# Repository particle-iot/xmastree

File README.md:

# PARTICLE CHRISTMAS TREE

It's a Happy Hardware Holiday for all! Meet the Particle Christmas Tree, a limited edition PCB packed full of cheer with customizable light patterns and holiday tunes. Use your tree with a Particle Photon or Electron to light up the LEDs and play music. Control your tree from the onboard joystick or from the Christmas Tree Web App.

Learn how to get started below. Happy Holidays from Team Particle!

## THINGS YOU'LL NEED
 - Christmas Tree
 - Micro USB cable
 - USB power supply (2A minimum rating)
 - Your Photon or Electron (new to Particle? Get started [here](https://docs.particle.io/guide/getting-started).)
 - Eggnog (optional)

## STEPS 

You can setup the tree in a matter of minutes.

1. Insert the Photon into the socket
1. Plug in the USB power supply
1. Flash [the Christmas tree firmware from the Web IDE][Firmware shared app] - no downloads required.
1. [Open the web interface][Web interface] and spread the cheer!

[Firmware shared app]: https://go.particle.io/shared_apps/5fc8c888e6f0b000092cf113
[Web interface]: https://particle-iot.github.io/xmastree

## GET TO KNOW YOUR TREE

### Joystick

The joystick is a 5 way button: up, down, left, right, and center (push in) then you can reprogram the usage any way you'd like. We have setup the button for you in the Christmas tree firmware to toggle light patterns and music.

|DIR   | PIN |
|:---  |:--- |
|UP    |D4| 
|DOWN  |A0|
|LEFT  |D5|
|RIGHT |D3|
|CENTER|D6|

### Dotstar RGB LEDs

The tree has 25 of the [APA102](http://www.led-color.com/upload/201604/APA102-2020%20SMD%20LED.pdf) 2020 RGB LEDs (also commonly known as dotstars) connected in a daisy chain. These LEDs are individually addressable using two pins, data and clock. These tiny stars are incredibly bright and fast. At full brightness, with all colors turned ON, each LED will consume about 60mA of current. So 25 of them will consume a max of 1.5Amp. This is why we recommend powering the tree with a **5VDC power supply that can source at least 2Amp.** Most modern USB phone chargers should be able to meet this demand.

### Photon/Electron Socket

The two dual-row headers allow you to use either the Particle Photon or the Electron. Please take care of the orientation and position of the device while plugging in.

### Piezo speaker

At the back of the tree you'll find a piezo speaker connected to pin D0. The firmware includes several 8-bit holiday tunes but you can also compose your own. This speaker can be a bit loud. If you'd like to reduce the volume, you can put a piece of tape on its opening.

### Headers for breadboarding

These pins breakout the power and control signal of the tree. You can mount the tree on a breadboard with the help of these pins. This will allow you to connect different hardware to your tree, daisy chain multiple trees, add more LEDs or even control it with other microcontrollers.

|PIN     |DESCRIPTION|
|:-------|:----------|
|D1      | Connected to the D1 pin of the Particle device and acts as CLOCK IN to the LEDs.|
|D2      | Connected to the D2 pin of the Particle device and acts as DATA IN to the LEDs.|
|DATA OUT| DATA OUT pin of the LEDs.|
|CLK OUT | CLOCK OUT pin of the LEDs.|
|VIN     | Input power to the tree and Particle device. This pin is connected to the VIN pin of the Particle device. 5VDC max .|
|GND     | Connected to the ground.|

## SETTING UP THE TREE 

You can either use a Particle Photon or an Electron to control the tree. Since the dotstar RGB LEDs work at 5VDC, you'll need to make sure that the USB cable is plugged in at all times to power the tree, unless you have powered the tree via a separate power source via the VIN pin.

> **NOTE:** When controlled by an Electron, the tree will not work with just the LiPo battery plugged in. You'll need to connect the USB cable as well or other external 5V DC power source.

## WAYS TO SET UP THE TREE

### As an ornament

The easiest way to setup the tree is to hang it as an ornament while powering over USB. You can also rig up your own 5V power supply cable and plug it into the header.

### On a breadboard

You can use the bottom header to mount the tree on a breadboard and power/control it via your own choice of hardware or to daisy chain the tree to other trees or dotstar projects.

## USING THE WEB INTERFACE

<p align="center">
</p>

There is [a hosted version of the web interface you can use to control your tree][Web interface]. Simply login with your Particle account, select your device and you'll be able to control the LEDs and music from a desktop or mobile browser.

## MODIFYING THE FIRMWARE

[][Firmware shared app]

Import the firmware to your Particle account in the Web IDE with the button above. You'll be
able to add new songs or tweak the functionality to your heart's
content.

Click [here](FIRMWARE.md) for more information about the Xmas Tree firmware.

## CONNECT

Having problems or have awesome suggestions? Connect with us on our [forum](https://community.particle.io/).

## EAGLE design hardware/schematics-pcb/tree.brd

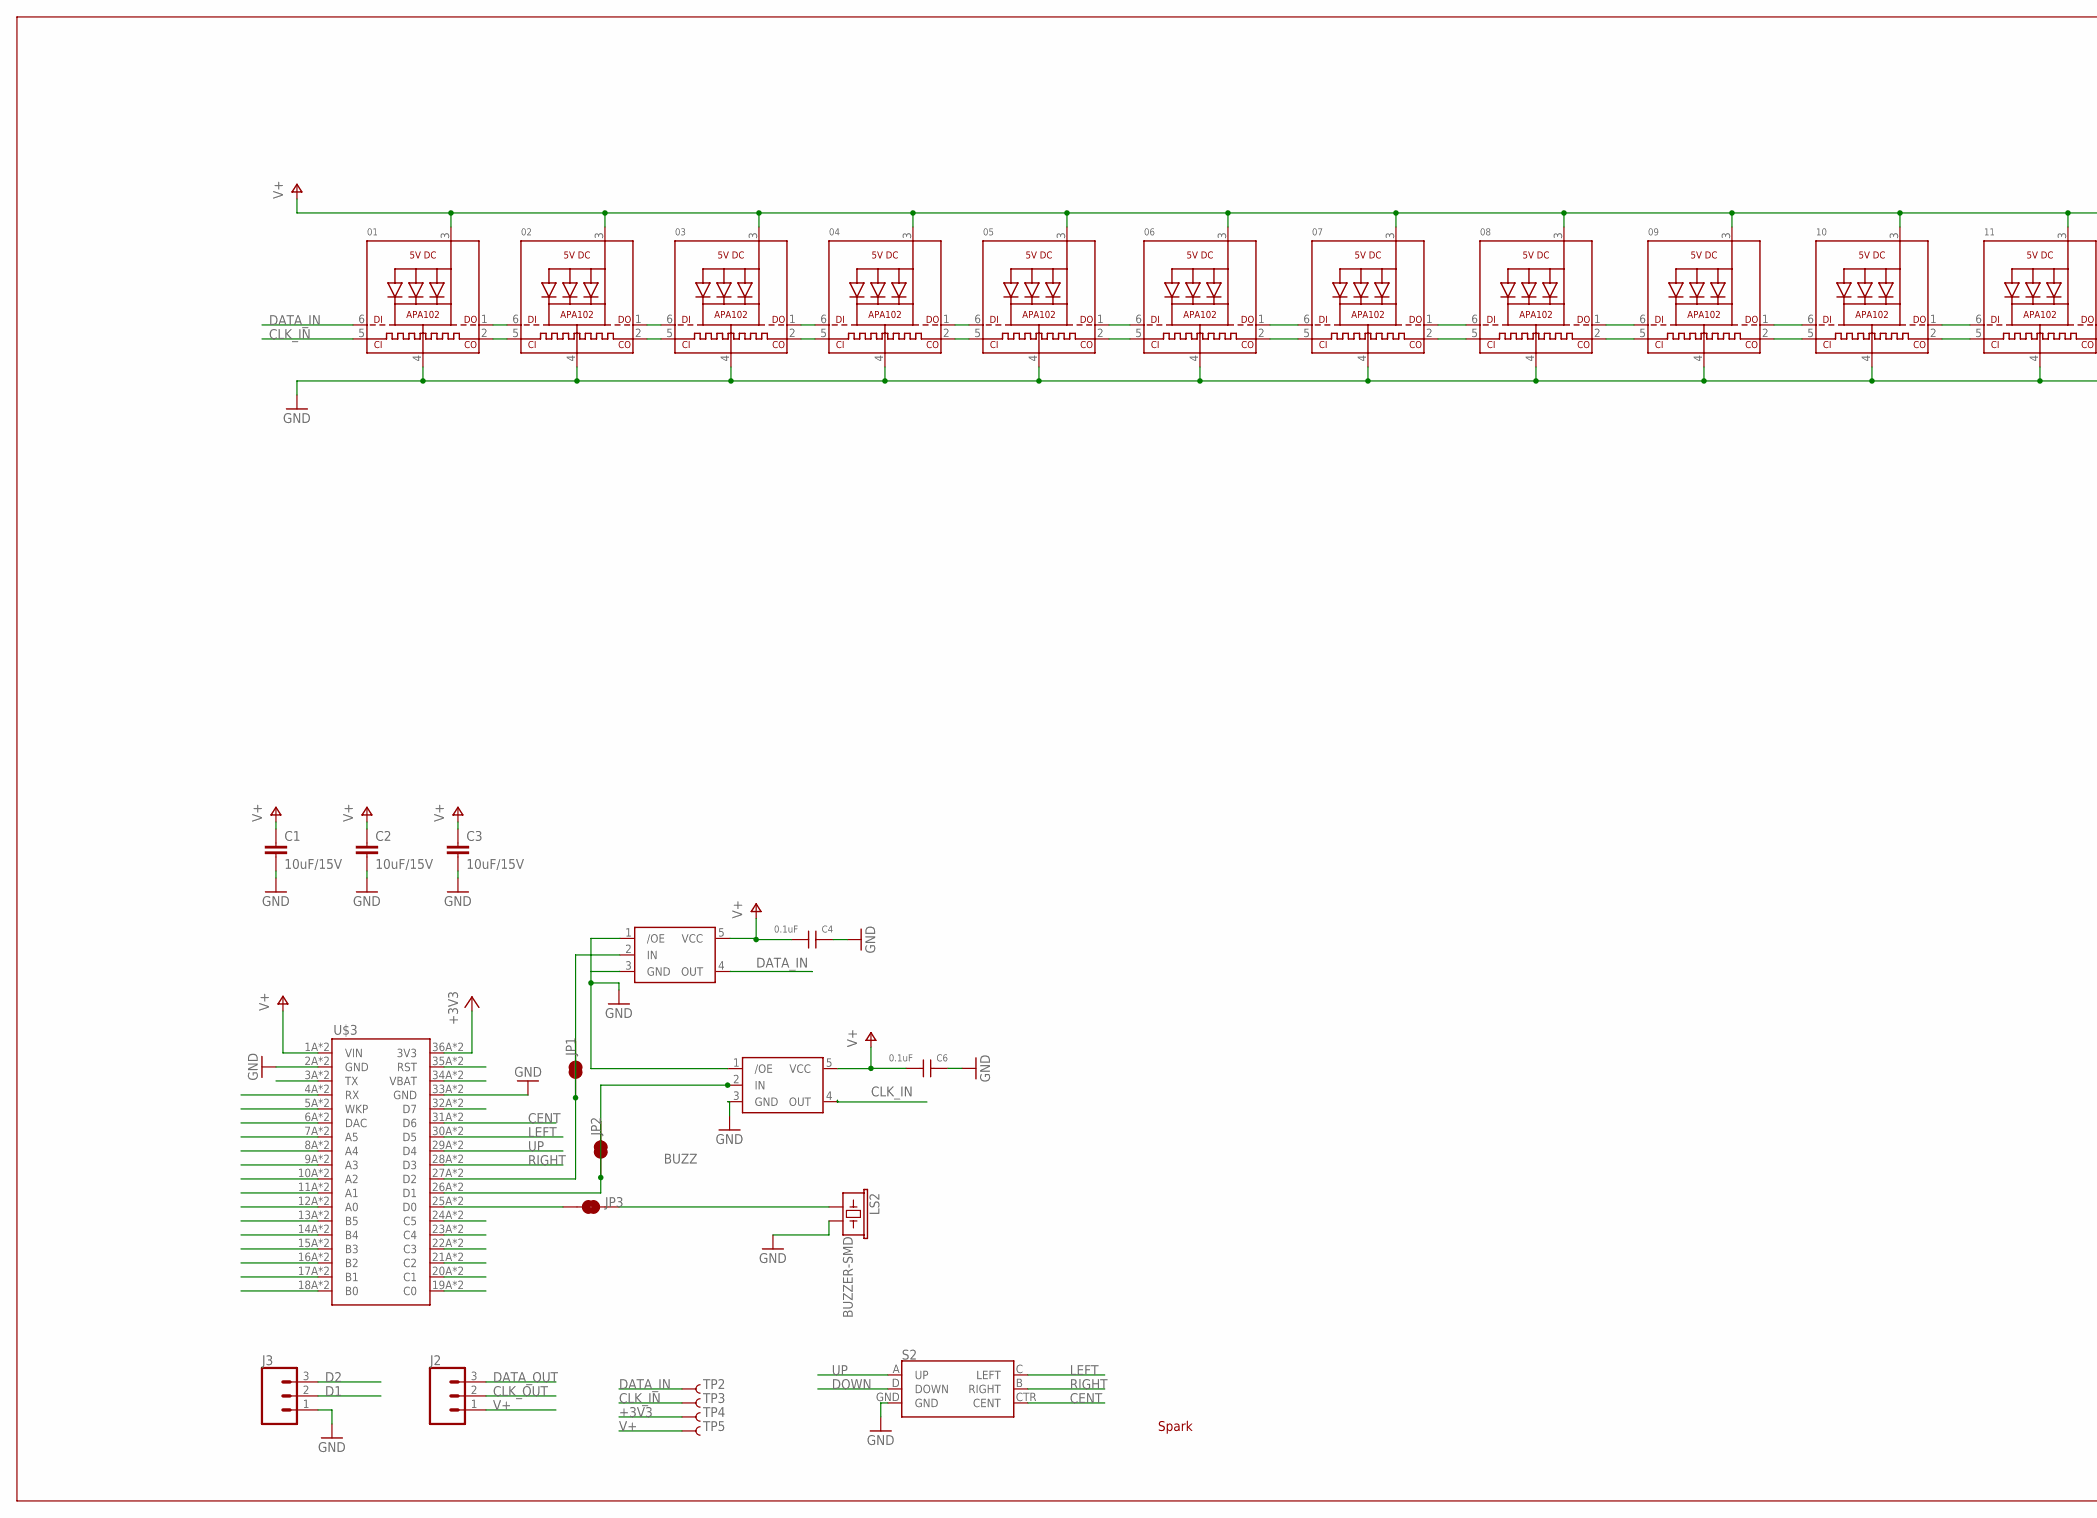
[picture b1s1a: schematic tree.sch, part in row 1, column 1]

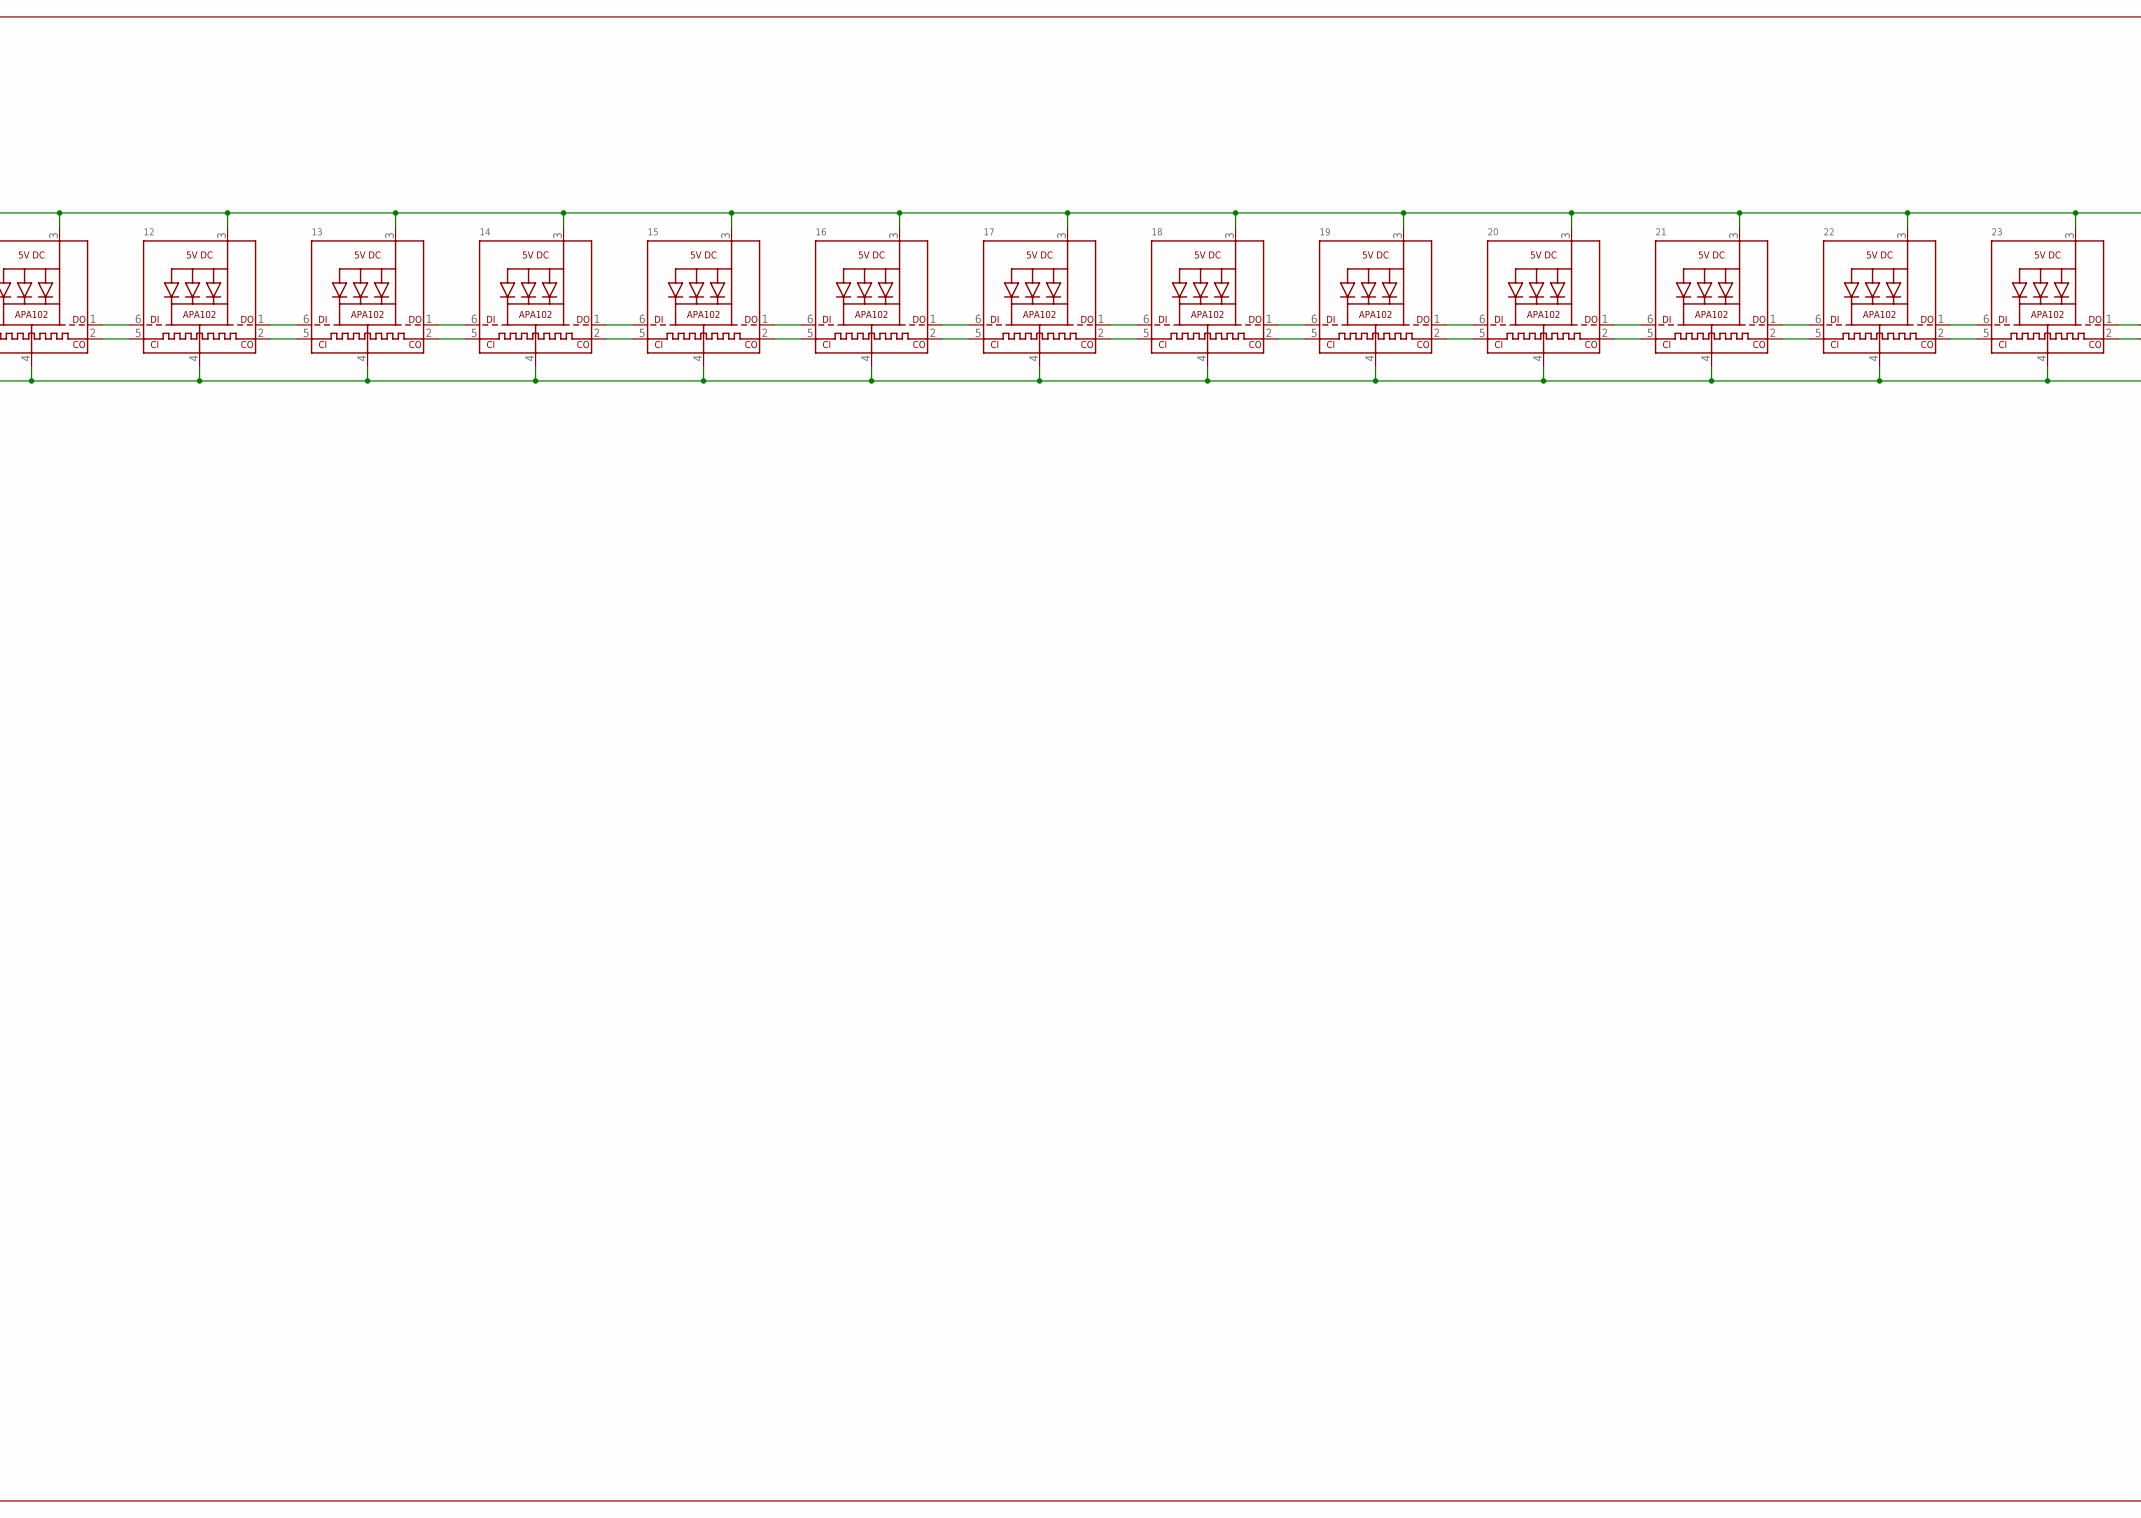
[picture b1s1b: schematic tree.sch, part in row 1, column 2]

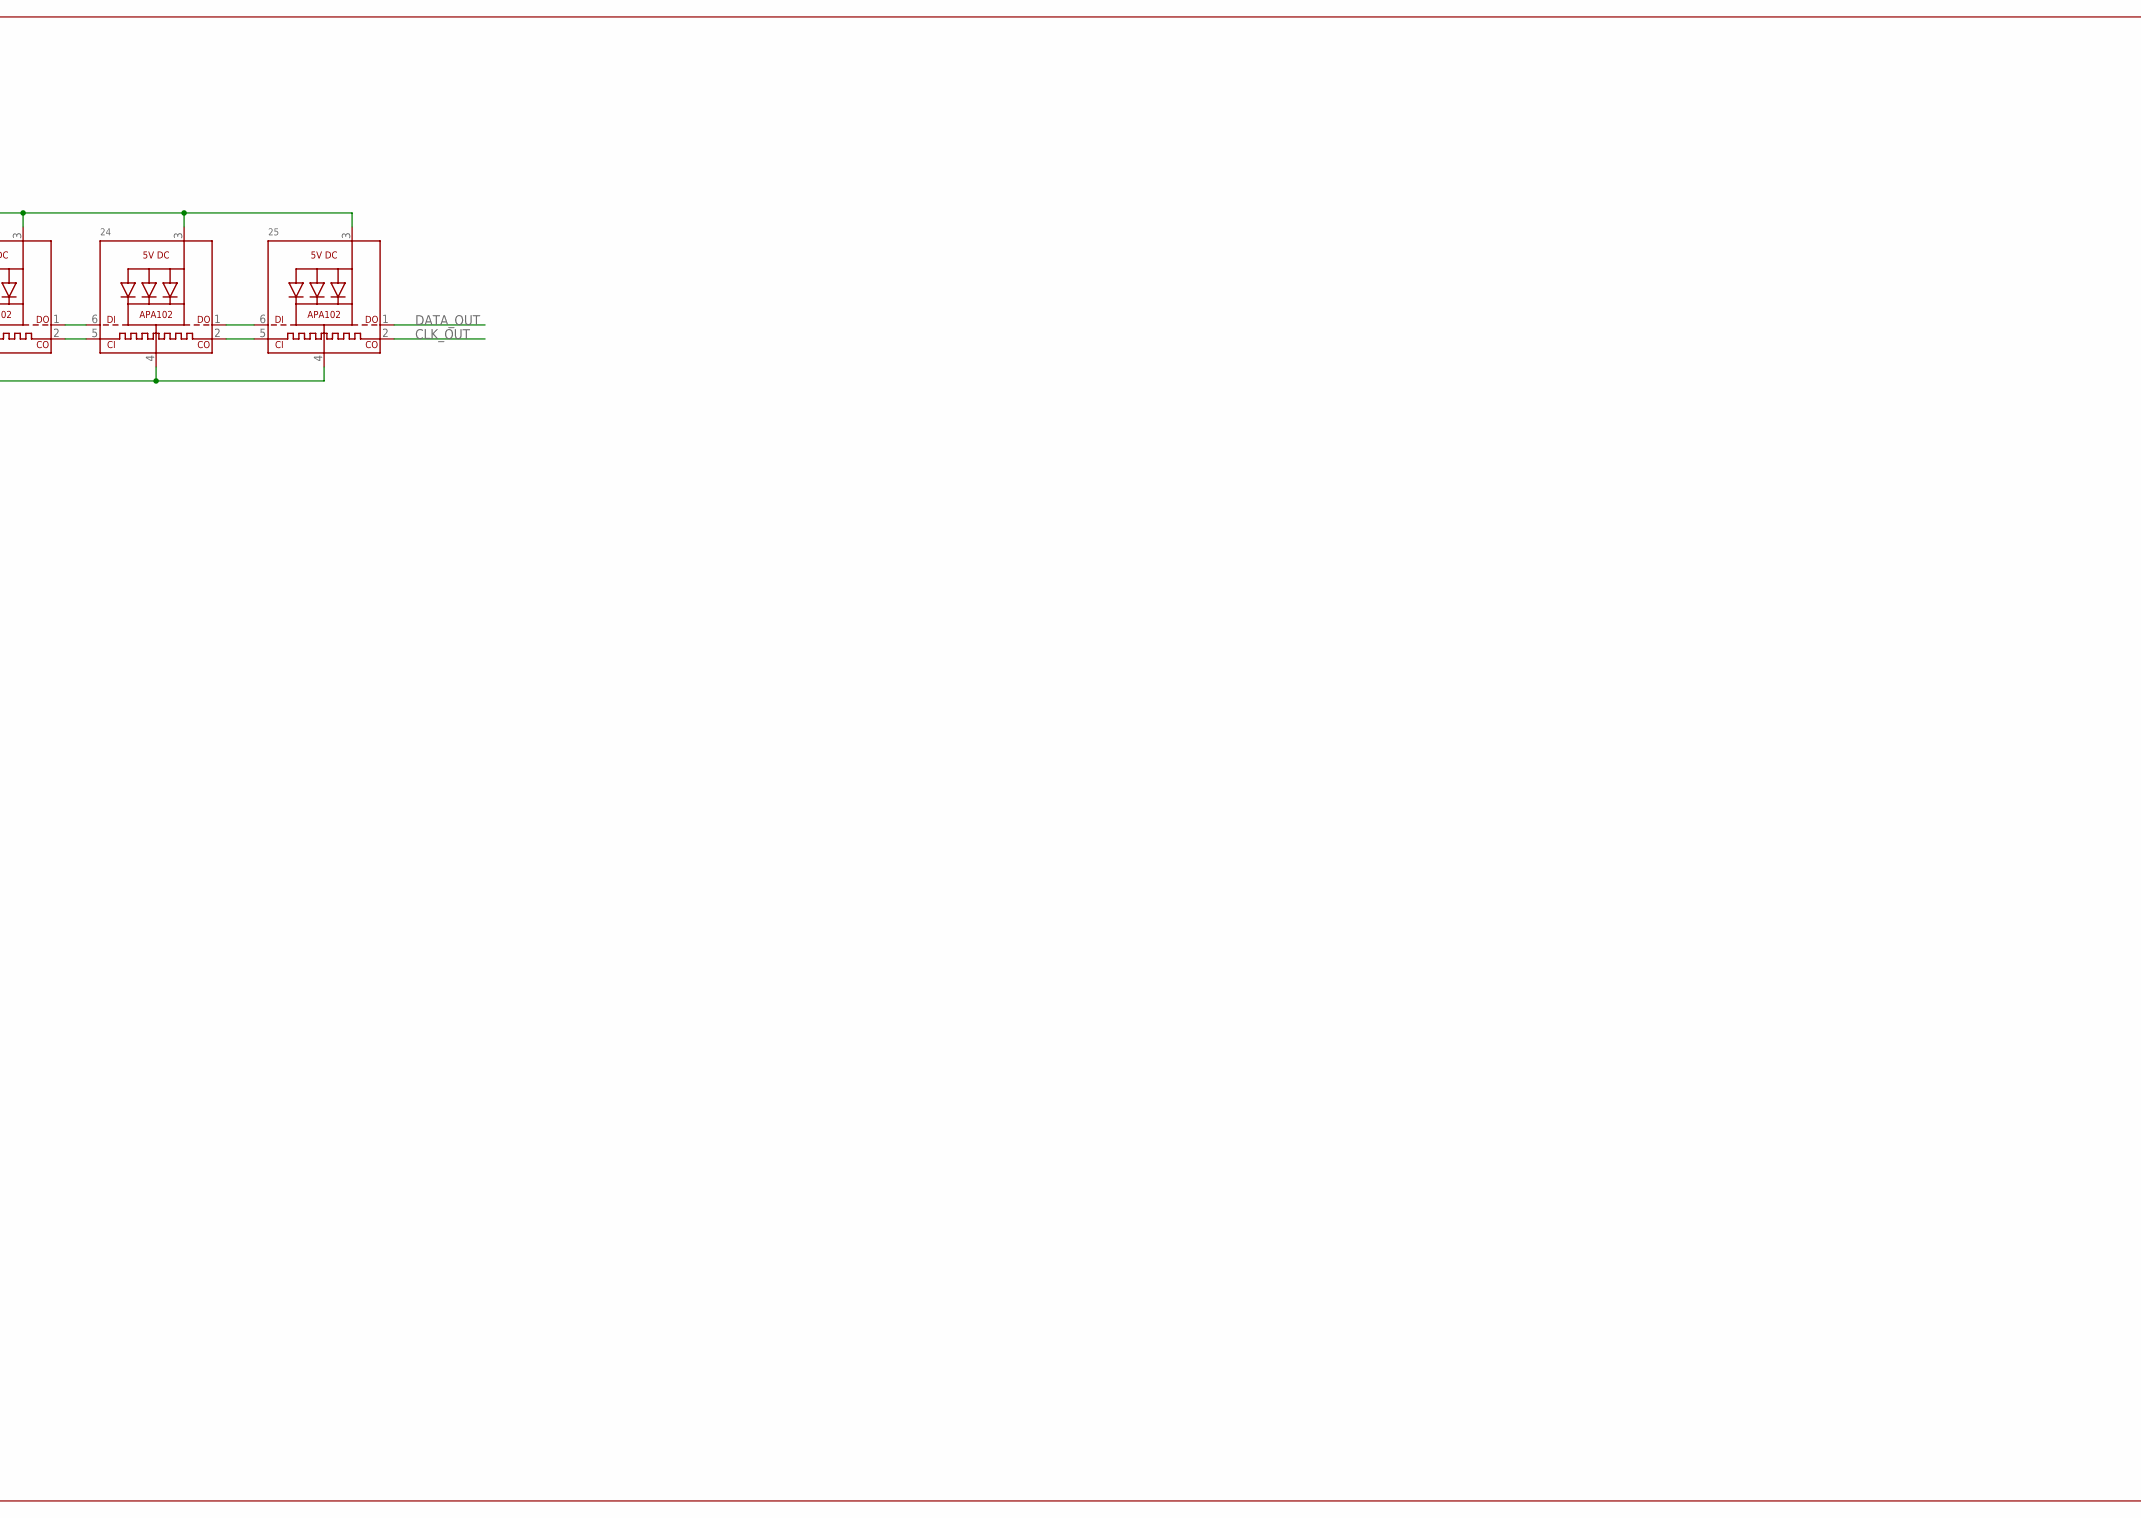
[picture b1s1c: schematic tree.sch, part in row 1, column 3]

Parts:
01, 02, 03, 04, 05, 06, 07, 08, 09, 10, 11, 12, 13, 14, 15, 16, 17, 18, 19, 20, 21, 22, 23, 24, 25: APA1022020; APA102_2020
C1, C2, C3: 10uF/15V; C0805K
C4, C6: 0.1uF; C-0603A
J2, J3: CONN_03; 1X03
JP1, JP2, JP3: JUMPER-SMT_2_NC_TRACE_NO-SILK; SMT-JUMPER_2_NC_TRACE_NO-SILK
LS2: BUZZER-SMD; BUZZER-CCV
S2: JOYSTICK_MINI
TP2, TP3, TP4, TP5: TEST-POINT3; PAD.03X.03
U1, U2: NL17SZ125; SOT-353
U$1: SPARK_LOGO; SPARK_LOGO_TSTOP
U$3: ELECTRON_SMT

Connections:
+3V3: TP4.P$1, U$3.36A (3V3), U$3.36B (3V3)
BUZZ: JP3.1, U$3.25A (D0), U$3.25B (D0)
CENT: S2.CTR (CENT), U$3.31A (D6), U$3.31B (D6)
CLK_IN: 01.5 (CKI), TP3.P$1, U2.4 (OUT)
CLK_OUT: 25.2 (CKO), J2.2
D1: J3.2, JP2.1, JP2.2, U2.2 (IN), U$3.26A (D1), U$3.26B (D1)
D2: J3.3, JP1.1, JP1.2, U1.2 (IN), U$3.27A (D2), U$3.27B (D2)
DATA_IN: 01.6 (DI), TP2.P$1, U1.4 (OUT)
DATA_OUT: 25.1 (DO), J2.3
DOWN: S2.D (DOWN), U$3.12A (A0), U$3.12B (A0)
GND: 01.4 (GND), 02.4 (GND), 03.4 (GND), 04.4 (GND), 05.4 (GND), 06.4 (GND), 07.4 (GND), 08.4 (GND), 09.4 (GND), 10.4 (GND), 11.4 (GND), 12.4 (GND), 13.4 (GND), 14.4 (GND), 15.4 (GND), 16.4 (GND), 17.4 (GND), 18.4 (GND), 19.4 (GND), 20.4 (GND), 21.4 (GND), 22.4 (GND), 23.4 (GND), 24.4 (GND), 25.4 (GND), C1.2, C2.2, C3.2, C4.2, C6.2, J3.1, LS2.- (2), S2.GND, U1.1 (/OE), U1.3 (GND), U2.1 (/OE), U2.3 (GND), U$3.2A (GND), U$3.2B (GND), U$3.33A (GND), U$3.33B (GND)
LEFT: S2.C (LEFT), U$3.30A (D5), U$3.30B (D5)
unnamed: U$3.24A (C5), U$3.24B (C5)
unnamed: JP3.2, LS2.+ (1)
unnamed: 01.1 (DO), 02.6 (DI)
unnamed: 01.2 (CKO), 02.5 (CKI)
unnamed: 02.1 (DO), 03.6 (DI)
unnamed: 02.2 (CKO), 03.5 (CKI)
unnamed: 03.1 (DO), 04.6 (DI)
unnamed: 03.2 (CKO), 04.5 (CKI)
unnamed: 04.1 (DO), 05.6 (DI)
unnamed: 04.2 (CKO), 05.5 (CKI)
unnamed: 05.1 (DO), 06.6 (DI)
unnamed: 05.2 (CKO), 06.5 (CKI)
unnamed: 06.1 (DO), 07.6 (DI)
unnamed: 06.2 (CKO), 07.5 (CKI)
unnamed: 07.1 (DO), 08.6 (DI)
unnamed: 07.2 (CKO), 08.5 (CKI)
unnamed: 08.1 (DO), 09.6 (DI)
unnamed: 08.2 (CKO), 09.5 (CKI)
unnamed: 09.1 (DO), 10.6 (DI)
unnamed: 09.2 (CKO), 10.5 (CKI)
unnamed: 10.1 (DO), 11.6 (DI)
unnamed: 10.2 (CKO), 11.5 (CKI)
unnamed: 11.1 (DO), 12.6 (DI)
unnamed: 11.2 (CKO), 12.5 (CKI)
unnamed: 12.2 (CKO), 13.5 (CKI)
unnamed: 12.1 (DO), 13.6 (DI)
unnamed: 13.1 (DO), 14.6 (DI)
unnamed: 13.2 (CKO), 14.5 (CKI)
unnamed: 14.1 (DO), 15.6 (DI)
unnamed: 14.2 (CKO), 15.5 (CKI)
unnamed: 15.1 (DO), 16.6 (DI)
unnamed: 15.2 (CKO), 16.5 (CKI)
unnamed: 16.1 (DO), 17.6 (DI)
unnamed: 16.2 (CKO), 17.5 (CKI)
unnamed: 17.1 (DO), 18.6 (DI)
unnamed: 17.2 (CKO), 18.5 (CKI)
unnamed: 18.1 (DO), 19.6 (DI)
unnamed: 18.2 (CKO), 19.5 (CKI)
unnamed: 19.1 (DO), 20.6 (DI)
unnamed: 19.2 (CKO), 20.5 (CKI)
unnamed: 20.1 (DO), 21.6 (DI)
unnamed: 20.2 (CKO), 21.5 (CKI)
unnamed: 21.1 (DO), 22.6 (DI)
unnamed: 21.2 (CKO), 22.5 (CKI)
unnamed: 22.1 (DO), 23.6 (DI)
unnamed: 22.2 (CKO), 23.5 (CKI)
unnamed: 23.1 (DO), 24.6 (DI)
unnamed: 23.2 (CKO), 24.5 (CKI)
unnamed: 24.1 (DO), 25.6 (DI)
unnamed: 24.2 (CKO), 25.5 (CKI)
unnamed: U$3.19A (C0), U$3.19B (C0)
unnamed: U$3.32A (D7), U$3.32B (D7)
unnamed: U$3.35A (RST), U$3.35B (RST)
unnamed: U$3.34A (VBAT), U$3.34B (VBAT)
unnamed: U$3.23A (C4), U$3.23B (C4)
unnamed: U$3.22A (C3), U$3.22B (C3)
unnamed: U$3.21A (C2), U$3.21B (C2)
unnamed: U$3.20A (C1), U$3.20B (C1)
unnamed: U$3.18A (B0), U$3.18B (B0)
unnamed: U$3.17A (B1), U$3.17B (B1)
unnamed: U$3.16A (B2), U$3.16B (B2)
unnamed: U$3.15A (B3), U$3.15B (B3)
unnamed: U$3.14A (B4), U$3.14B (B4)
unnamed: U$3.13A (B5), U$3.13B (B5)
unnamed: U$3.11A (A1), U$3.11B (A1)
unnamed: U$3.10A (A2), U$3.10B (A2)
unnamed: U$3.9A (A3), U$3.9B (A3)
unnamed: U$3.8A (A4), U$3.8B (A4)
unnamed: U$3.7A (A5), U$3.7B (A5)
unnamed: U$3.6A (DAC), U$3.6B (DAC)
unnamed: U$3.5A (WKP), U$3.5B (WKP)
unnamed: U$3.4A (RX), U$3.4B (RX)
unnamed: U$3.3A (TX), U$3.3B (TX)
RIGHT: S2.B (RIGHT), U$3.28A (D3), U$3.28B (D3)
UP: S2.A (UP), U$3.29A (D4), U$3.29B (D4)
V+: 01.3 (VDD), 02.3 (VDD), 03.3 (VDD), 04.3 (VDD), 05.3 (VDD), 06.3 (VDD), 07.3 (VDD), 08.3 (VDD), 09.3 (VDD), 10.3 (VDD), 11.3 (VDD), 12.3 (VDD), 13.3 (VDD), 14.3 (VDD), 15.3 (VDD), 16.3 (VDD), 17.3 (VDD), 18.3 (VDD), 19.3 (VDD), 20.3 (VDD), 21.3 (VDD), 22.3 (VDD), 23.3 (VDD), 24.3 (VDD), 25.3 (VDD), C1.1, C2.1, C3.1, C4.1, C6.1, J2.1, TP5.P$1, U1.5 (VCC), U2.5 (VCC), U$3.1A (VIN), U$3.1B (VIN)

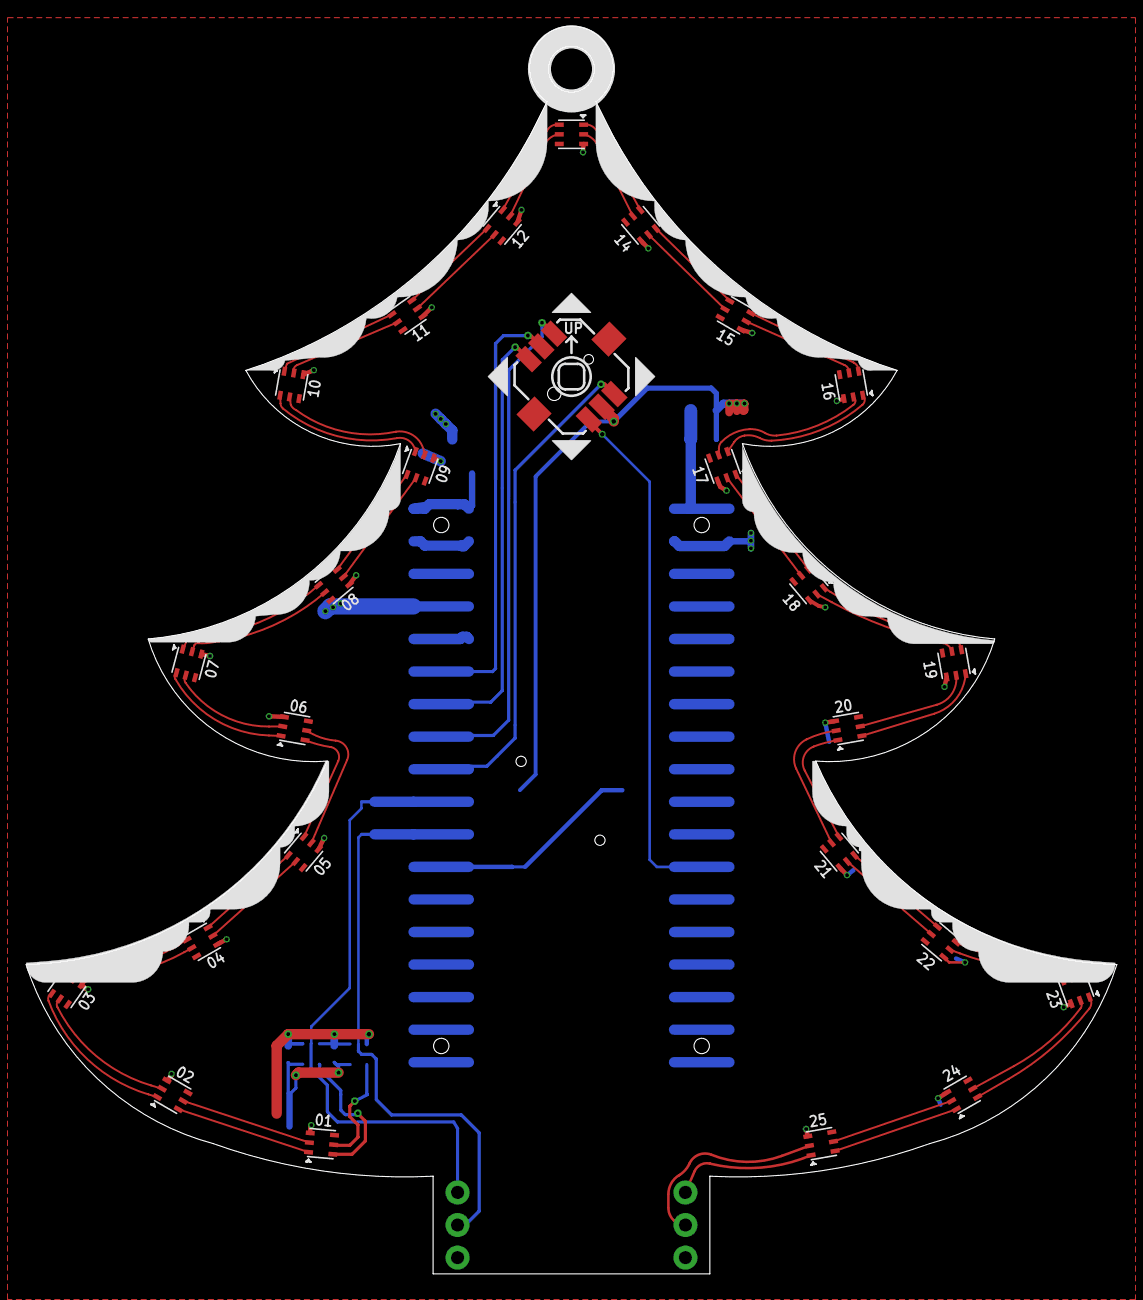
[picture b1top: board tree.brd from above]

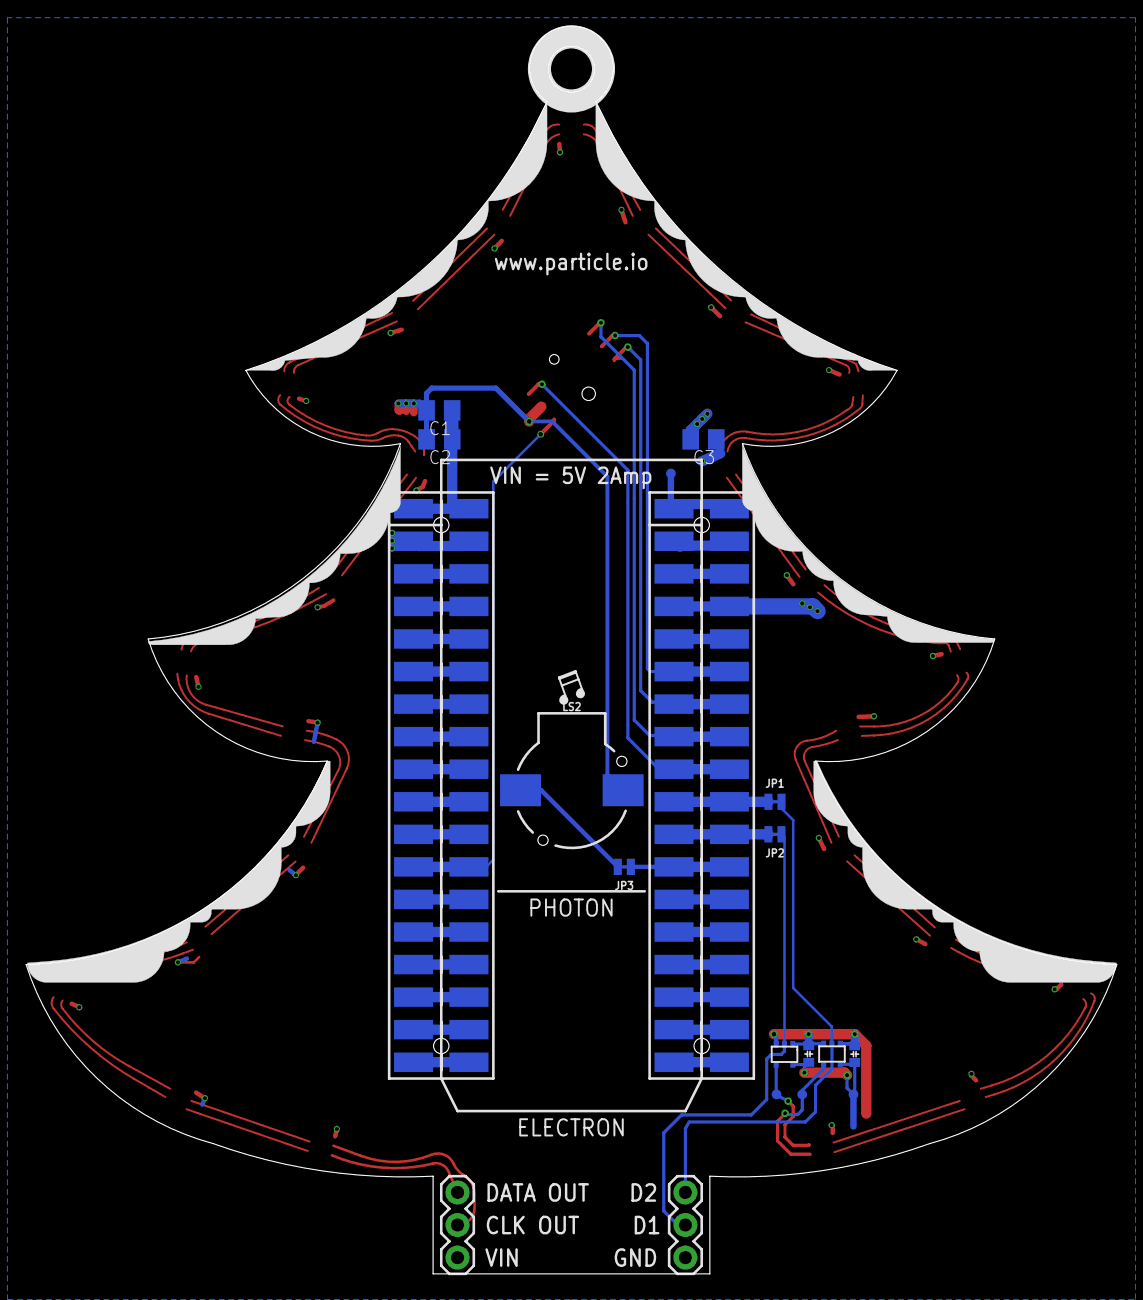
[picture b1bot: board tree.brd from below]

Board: 2 copper layers, 85.1 x 97.3 mm, 45 parts (18 on the bottom side), 88 nets.

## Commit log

2017-12-08 🎄🎄🎄❄️⛄️🤶 v1 🎅⛄️❄️🎄🎄🎄
2017-12-08 fix minor typos in README
2017-12-10 D4 🎵
2017-12-10 Clarify setup instructions
2017-12-15 Change LED color ordering and add red on green animation
    Fixes #1
2017-12-16 Updated URL to the latest firmware and added a new song - Silent Night.
2017-12-18 A correct practice for adding songs, also some minor fixes.
2017-12-24 Add animation pattern: Spark with Particle Cyan.
2018-01-03 org-rename
2018-01-03 update GH page links to use new particle-iot subdomain https://spark.github.io/xmastree -> https://particle-iot.github.io/xmastree
2018-01-03 update client id to one which uses particle-iot redirect_url
2018-01-03 update git repo urls to use new particle-iot path
2018-01-03 update config docs
2018-01-03 deploy app
2018-01-03 1.0.1
2018-02-04 gernerated --> generated
2020-12-03 Update WebIDE Link

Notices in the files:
parts and their libraries:
microbuilder: This work is placed in the public domain, and may be freely used for commercial and non-commercial work with the following conditions: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
SparkFun-Connectors: Licensing: Creative Commons ShareAlike 4.0 International - https://creativecommons.org/licenses/by-sa/4.0
